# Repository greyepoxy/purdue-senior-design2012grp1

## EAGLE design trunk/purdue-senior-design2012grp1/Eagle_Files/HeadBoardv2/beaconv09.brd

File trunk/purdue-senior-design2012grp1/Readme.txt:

Please place code for the different chips in different folders with the chip name or an alias as the name of the folder. 
Also please place schematic drawings and PCB files in these folders as well.

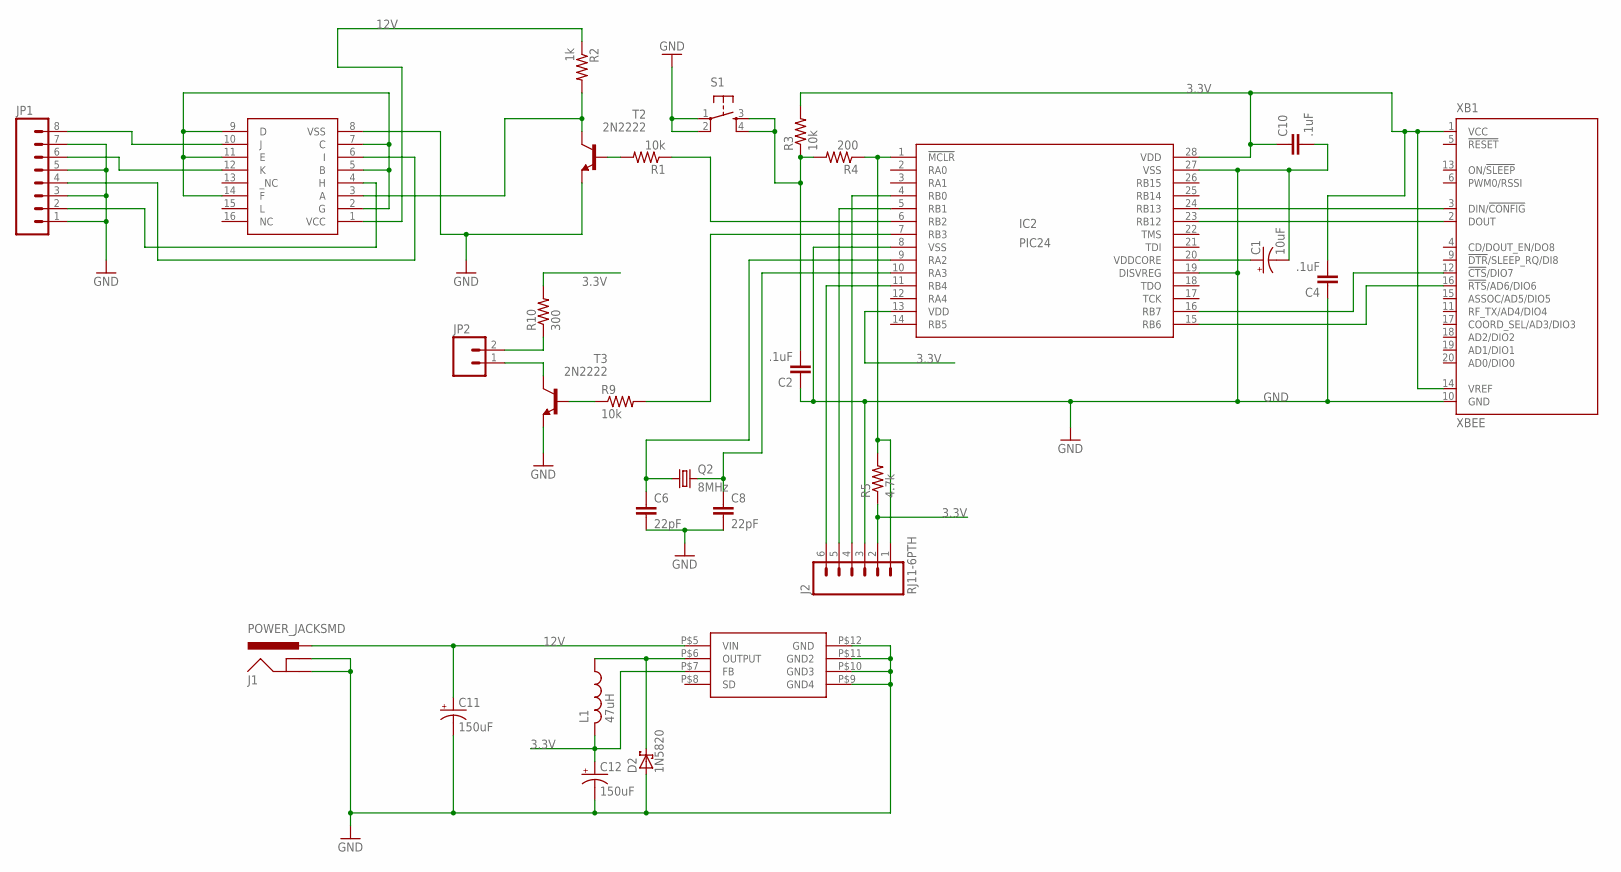
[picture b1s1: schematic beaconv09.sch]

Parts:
AP1509: BUCK1; BUCK
C1: 10uF; EIA3216
C2, C4, C10: .1uF; C1206
C6, C8: 22pF; C1206
C11, C12: 150uF; ECAPSMPS
D2: 1N5820; DO201T15
IC2: PIC24; SO28W
J1: POWER_JACKSMD; POWER_JACK_SMD
J2: RJ11-6PTH; RJ11-6
JP1: M08LOCK; 1X08_LOCK
JP2: M02LOCK; 1X02_LOCK
L1: 47uH; BUCKINDUCTOR2
Q2: 8MHz; HC49UP
R1, R3: 10k; 1206
R2: 1k; 1206
R4: 200; 1206
R5: 4.7k; R1206
R9: 10k; R1206
R10: 300; R1206
S1: TAC_SWITCHSMD; TACTILE_SWITCH_SMD
T2, T3: 2N2222; TO92-CBE
U$2: CD4049; DIL16
XB1: XBEE

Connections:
3.3V: AP1509.P$7 (FB), C4.2, C10.1, C12.P$1 (+), IC2.13 (VDD), IC2.28 (VDD), J2.2, L1.P$2 (2), R3.2, R5.1, R10.2, XB1.1 (VCC), XB1.14 (VREF)
12V: AP1509.P$5 (VIN), C11.P$1 (+), J1.VIN0 (PWR), R2.1, U$2.1 (VCC)
GND: AP1509.P$9 (GND4), AP1509.P$10 (GND3), AP1509.P$11 (GND2), AP1509.P$12 (GND), C1.C (-), C2.1, C4.1, C6.2, C8.2, C10.2, C11.P$2 (-), C12.P$2 (-), D2.A, IC2.8 (VSS), IC2.19 (DISVREG), IC2.27 (VSS), J1.GND (GNDBREAK), J1.P$4 (GND), J2.3, JP1.1, JP1.3, JP1.5, JP1.7, S1.1, S1.2, T2.E, T3.E, U$2.8 (VSS), XB1.10 (GND)
unnamed: IC2.6 (RB2), R1.1
unnamed: R1.2, T2.B
unnamed: JP1.2, U$2.4 (H)
unnamed: JP2.2, R10.1
unnamed: JP1.4, U$2.6 (I)
unnamed: IC2.23 (RB12), XB1.2 (DOUT)
unnamed: JP1.8, U$2.10 (J)
unnamed: IC2.24 (RB13), XB1.3 (DIN/!CONFIG)
unnamed: IC2.4 (RB0), J2.4
unnamed: C1.A (+), IC2.20 (VDDCORE)
unnamed: C2.2, R3.1, R4.2, S1.3, S1.4
unnamed: IC2.1 (!MCLR), J2.1, R4.1, R5.2
unnamed: IC2.16 (RB7), XB1.12 (!CTS!/DIO7)
unnamed: AP1509.P$6 (OUTPUT), D2.C, L1.P$1 (1)
unnamed: R2.2, T2.C, U$2.3 (A)
unnamed: IC2.7 (RB3), R9.2
unnamed: JP1.6, U$2.12 (K)
unnamed: JP2.1, T3.C
unnamed: IC2.5 (RB1), J2.5
unnamed: IC2.11 (RB4), J2.6
unnamed: U$2.2 (G), U$2.5 (B), U$2.7 (C), U$2.9 (D), U$2.11 (E), U$2.14 (F)
unnamed: C6.1, IC2.9 (RA2), Q2.1
unnamed: IC2.15 (RB6), XB1.16 (!RTS!/AD6/DIO6)
unnamed: C8.1, IC2.10 (RA3), Q2.2
unnamed: R9.1, T3.B

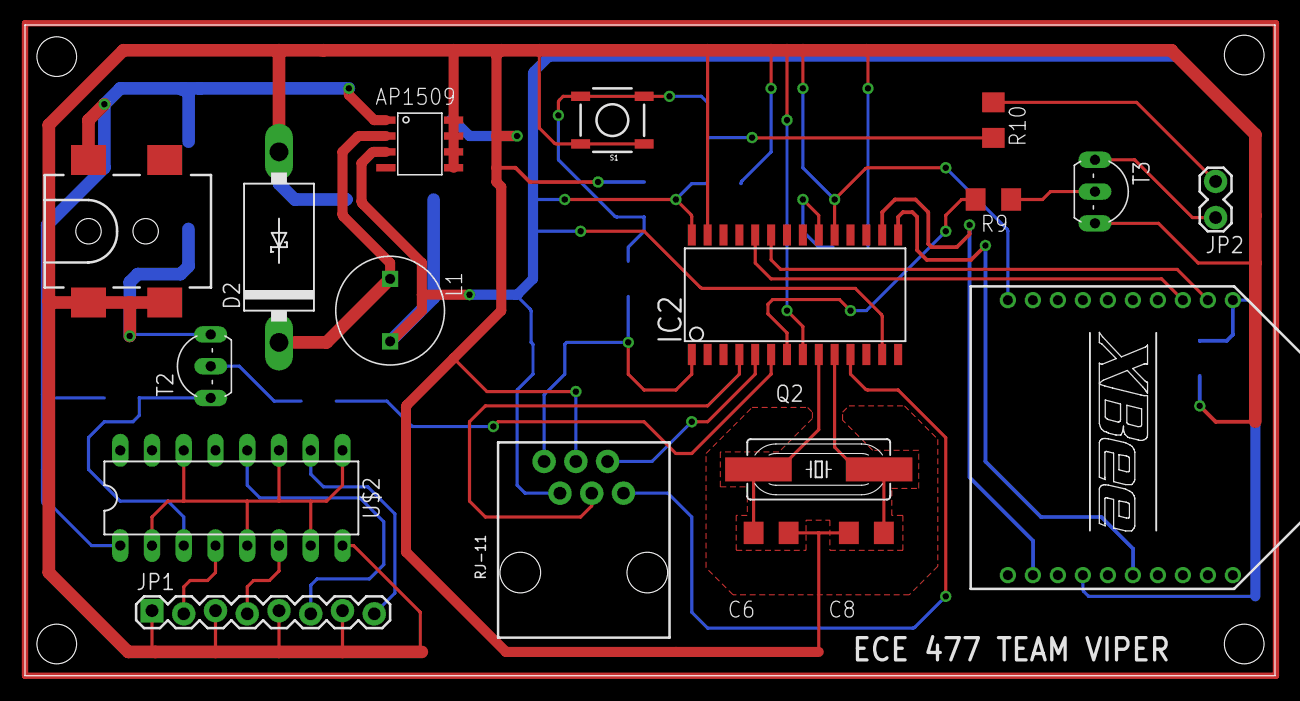
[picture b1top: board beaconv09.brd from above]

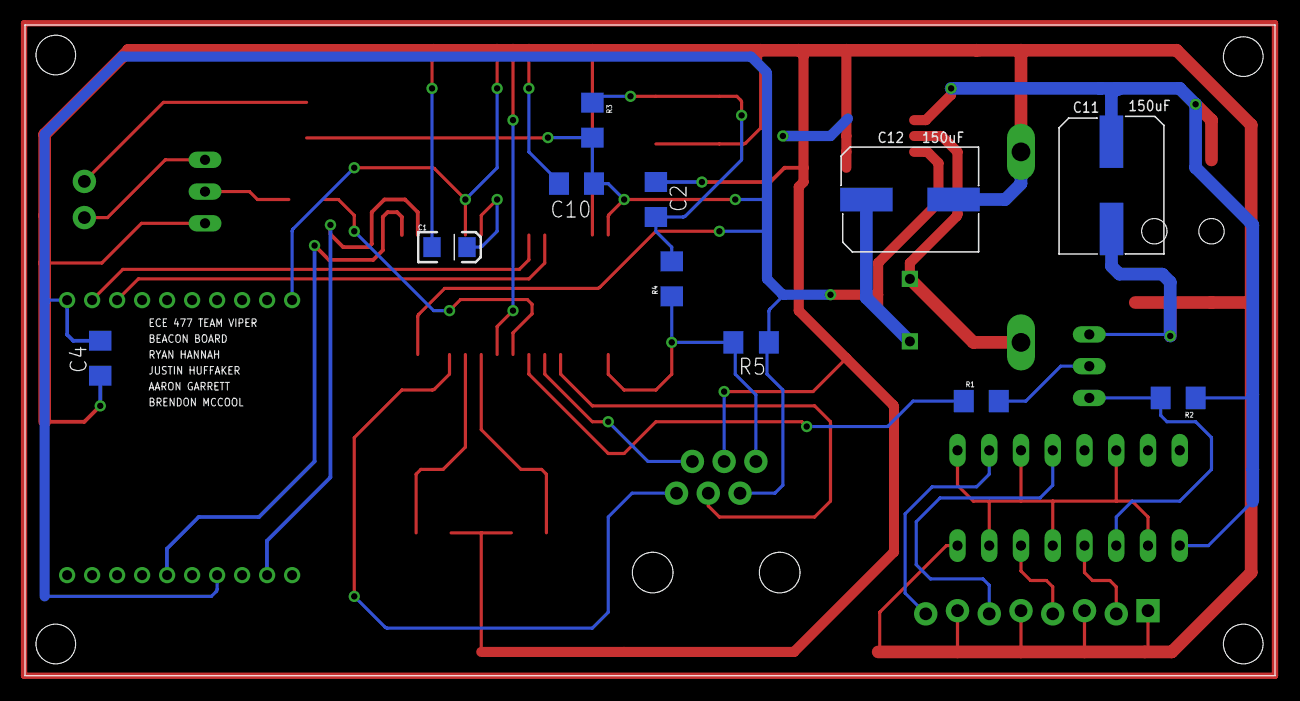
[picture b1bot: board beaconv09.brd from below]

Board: 2 copper layers, 100.0 x 52.1 mm, 29 parts (11 on the bottom side), 28 nets.

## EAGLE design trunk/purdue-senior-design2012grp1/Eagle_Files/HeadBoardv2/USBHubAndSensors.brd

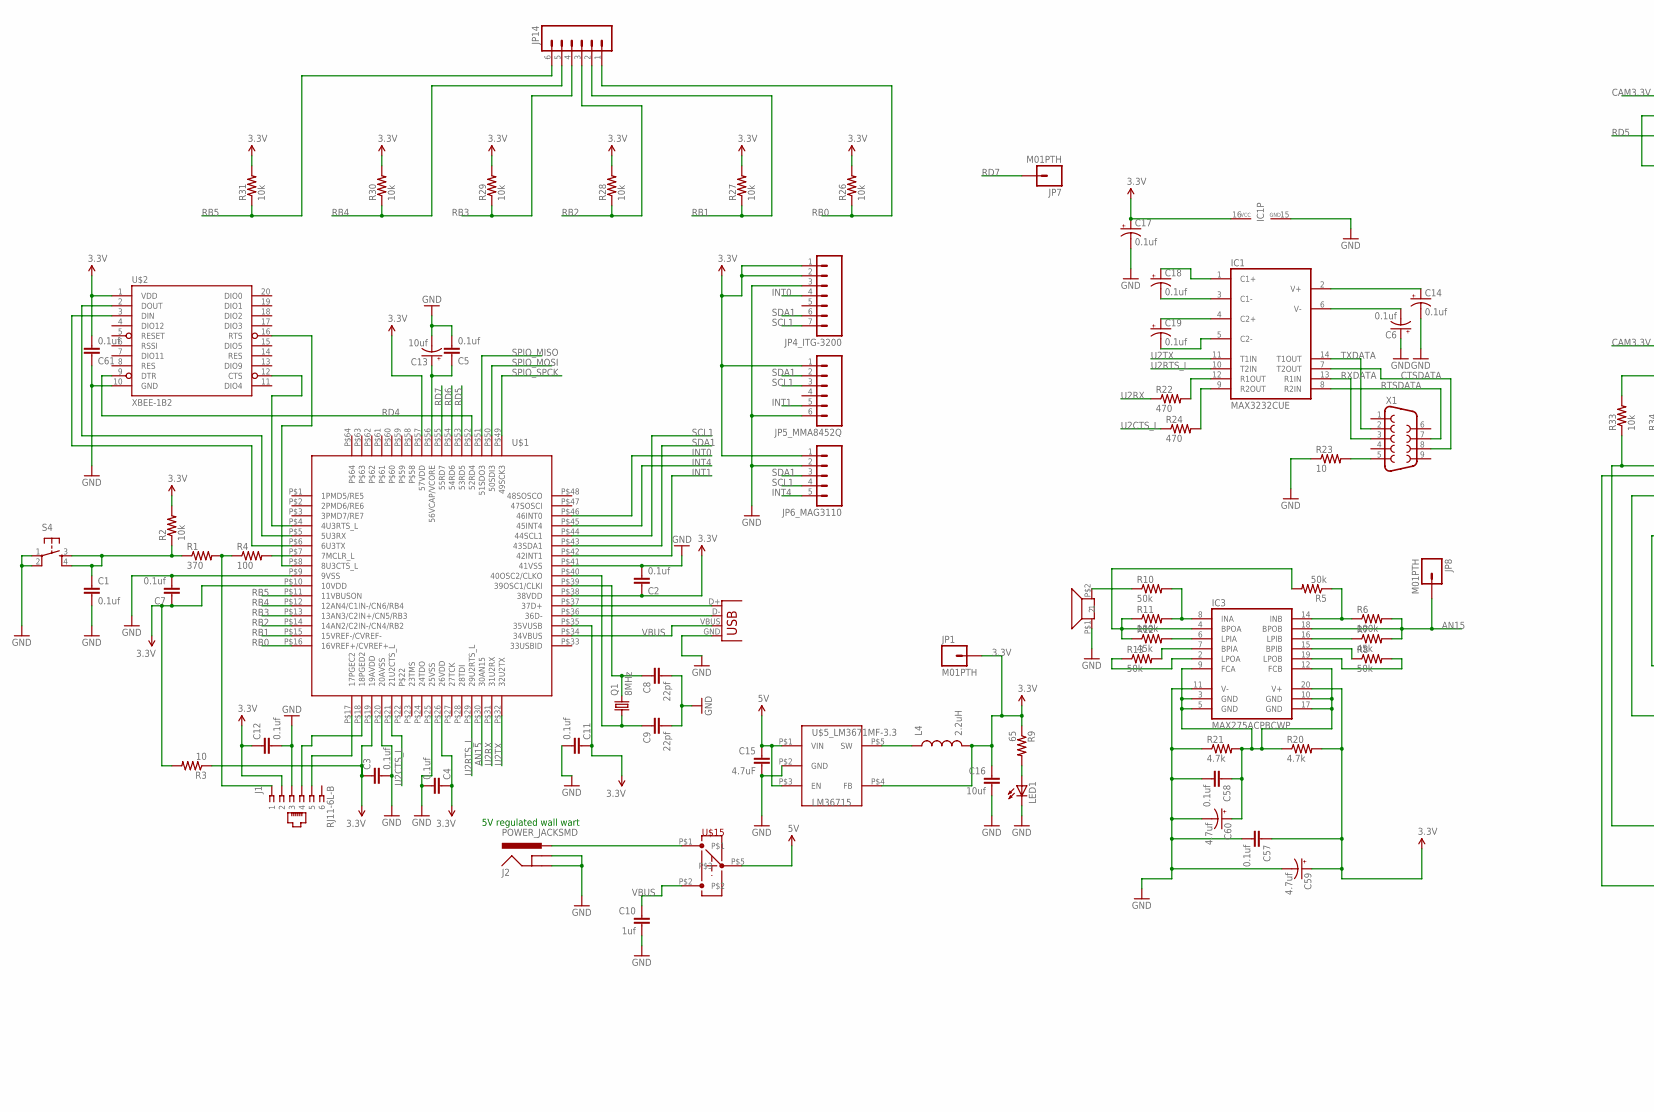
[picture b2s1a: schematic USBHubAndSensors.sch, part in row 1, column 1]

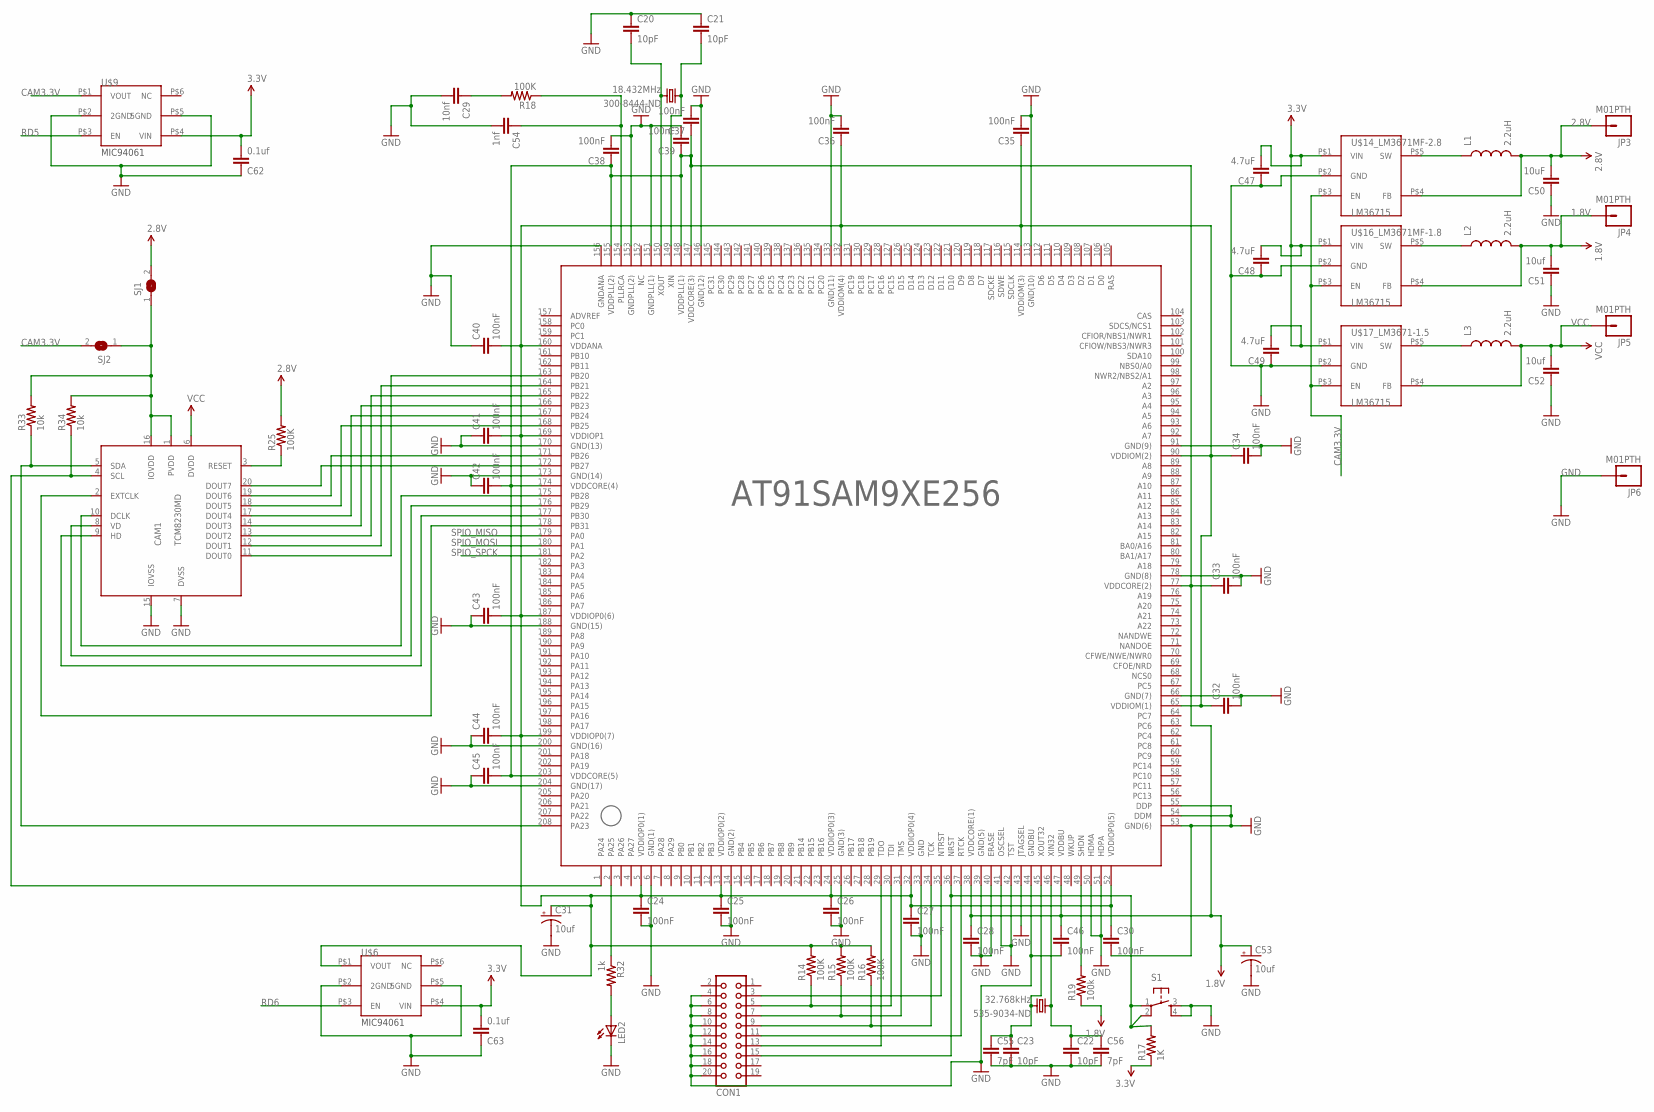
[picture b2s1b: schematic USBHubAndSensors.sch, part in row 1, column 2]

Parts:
300-8444-ND: 18.432MHz; TC38H
535-9034-ND: 32.768kHz; TC38H
C1, C2, C3, C4, C5, C7, C11, C12, C57, C58, C61, C62, C63: 0.1uf; 1206
C6, C14, C17, C18, C19: 0.1uf; EIA3216
C8, C9: 22pf; 1206
C10: 1uf; 1206
C13, C31, C53: 10uf; EIA3216
C15, C47, C48, C49: 4.7uF; 1206
C16, C51, C52: 10uf; 1206
C20, C21, C22, C23: 10pF; 1206
C24, C25, C26, C27, C28, C30, C32, C33, C34, C35, C36, C37, C38, C39, C40, C41, C42, C43, C44, C45, C46: 100nF; 1206
C29: 10nf; 1206
C50: 10uF; 1206
C54: 1nf; 1206
C55, C56: 7pF; 1206
C59, C60: 4.7uf; EIA3216
CAM1: TCM8230MD
CON1: CON20
IC1: MAX3232CUE; TSSOP16
IC3: MAX275ACPBCWP; SO20L
J1: RJ11-6L-B; RJ11-NO_SHIELD
J2: POWER_JACKSMD; POWER_JACK_SMD
JP1, JP3, JP4, JP5, JP6, JP7, JP8: M01PTH; 1X01
JP4_ITG-3200: M07; 1X07
JP5_MMA8452Q, JP14: M06SIP; 1X06
JP6_MAG3110: M05PTH; 1X05
L1, L2, L3, L4: 2.2uH; 1210
LED1, LED2: LED-FKIT-1206; FKIT-LED-1206
Q1: 8MHz; HC49UP
R1: 370; 1206
R2, R26, R27, R28, R29, R30, R31, R33, R34: 10k; 1206
R3, R23: 10; 1206
R4: 100; 1206
R5, R8, R10, R13: 50k; 1206
R6, R11, R19: 100k; 1206
R7, R12: 45k; 1206
R9: 65; 1206
R14, R15, R16, R18, R25: 100K; 1206
R17: 1K; 1206
R20, R21: 4.7k; 1206
R22, R24: 470; 1206
R32: 1k; 1206
S1, S4: TAC_SWITCHPTH; TACTILE-PTH
SJ1, SJ2: SJ
U$1: PIC32MX534F06HTQFP; 64-TQFP
U$2: XBEE-1B2; XBEE-SILK
U$5: 40TR-12B; 40TR
U$5_LM3671MF-3.3, U$14_LM3671MF-2.8, U$16_LM3671MF-1.8, U$17_LM3671-1.5: LM36715; SOT23-5
U$6, U$9: MIC94061YC6; SC-70-6
U$7: AT91SAM9XE256; PQFP208
U$15: G-107PLUG-IN; G-197
X1: DB9FEMALE; DB9
X2: USB-MICROB

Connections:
1.8V: C28.1, C33.1, C37.1, C38.1, C39.1, C42.2, C45.2, C46.1, C51.2, C53.A (+), JP4.1, L2.2, R19.1, U$7.38 (VDDCORE(1)), U$7.47 (VDDBU), U$7.77 (VDDCORE(2)), U$7.147 (VDDCORE(3)), U$7.148 (VDDPLL(1)), U$7.155 (VDDPLL(2)), U$7.174 (VDDCORE(4)), U$7.203 (VDDCORE(5)), U$16_LM3671MF-1.8.P$4 (FB)
2.8V: C50.2, JP3.1, L1.2, R25.2, SJ1.2, U$14_LM3671MF-2.8.P$4 (FB)
3.3V: C2.1, C3.1, C4.1, C7.1, C11.1, C12.1, C16.1, C17.A (+), C47.2, C48.2, C49.2, C57.1, C59.A (+), C61.2, C62.2, C63.2, IC1.16 (VCC), IC3.20 (V+), J1.2, JP1.1, JP4_ITG-3200.1, JP4_ITG-3200.2, JP5_MMA8452Q.1, JP6_MAG3110.1, L4.2, R2.2, R3.1, R3.2, R9.1, R17.1, R20.2, R26.2, R27.2, R28.2, R29.2, R30.2, R31.2, U$1.P$10 (10VDD), U$1.P$19 (19AVDD), U$1.P$26 (26VDD), U$1.P$35 (35VUSB), U$1.P$38 (38VDD), U$1.P$57 (57VDD), U$2.1 (VDD), U$5_LM3671MF-3.3.P$4 (FB), U$6.P$4 (VIN), U$9.P$4 (VIN), U$14_LM3671MF-2.8.P$1 (VIN), U$16_LM3671MF-1.8.P$1 (VIN), U$17_LM3671-1.5.P$1 (VIN)
5V: C15.1, U$5_LM3671MF-3.3.P$1 (VIN), U$5_LM3671MF-3.3.P$3 (EN), U$15.P$5
AN15: IC3.18 (BPOB), JP8.1, R6.2, R7.2, U$1.P$30 (30AN15)
CAM3.3V: SJ2.2, U$9.P$1 (VOUT), U$14_LM3671MF-2.8.P$3 (EN), U$16_LM3671MF-1.8.P$3 (EN), U$17_LM3671-1.5.P$3 (EN)
CTSDATA: IC1.7 (T2OUT), X1.8
GND: C1.2, C2.2, C3.2, C4.2, C5.2, C6.A (+), C7.2, C8.2, C9.2, C10.2, C11.2, C12.2, C13.C (-), C14.C (-), C15.2, C16.2, C17.C (-), C20.1, C21.1, C22.2, C23.2, C24.2, C25.2, C26.2, C27.2, C28.2, C29.2, C30.2, C31.C (-), C32.2, C33.2, C34.2, C35.2, C36.2, C37.2, C38.2, C39.2, C40.1, C41.1, C42.1, C43.1, C44.1, C45.1, C46.2, C47.1, C48.1, C49.1, C50.1, C51.1, C52.1, C53.C (-), C54.2, C55.2, C56.2, C57.2, C58.2, C59.C (-), C60.C (-), C61.1, C62.1, C63.1, CAM1.7 (DVSS), CAM1.15 (IOVSS), CON1.4, CON1.6, CON1.8, CON1.10, CON1.12, CON1.14, CON1.16, CON1.18, CON1.20, IC1.15 (GND), IC3.11 (V-), J1.3, J2.GND (GNDBREAK), J2.P$4 (GND), JP4_ITG-3200.3, JP5_MMA8452Q.6, JP6.1, JP6_MAG3110.2, LED1.C, LED2.C, R21.1, R23.1, S1.3, S1.4, S4.1, S4.2, U$1.P$9 (9VSS), U$1.P$20 (20AVSS), U$1.P$25 (25VSS), U$1.P$41 (41VSS), U$2.10 (GND), U$5.P$1 (1), U$5_LM3671MF-3.3.P$2 (GND), U$6.P$2 (2GND), U$6.P$5 (5GND), U$7.6 (GND(1)), U$7.14 (GND(2)), U$7.25 (GND(3)), U$7.33 (GND), U$7.39 (GND(5)), U$7.40 (ERASE), U$7.41 (OSCSEL), U$7.42 (TST), U$7.43 (JTAGSEL), U$7.44 (GNDBU), U$7.50 (HDMA), U$7.51 (HDPA), U$7.53 (GND(6)), U$7.54 (DDM), U$7.55 (DDP), U$7.66 (GND(7)), U$7.78 (GND(8)), U$7.91 (GND(9)), U$7.113 (GND(10)), U$7.133 (GND(11)), U$7.146 (GND(12)), U$7.151 (GNDPLL(1)), U$7.153 (GNDPLL(2)), U$7.156 (GNDANA), U$7.170 (GND(13)), U$7.173 (GND(14)), U$7.188 (GND(15)), U$7.200 (GND(16)), U$7.204 (GND(17)), U$9.P$2 (2GND), U$9.P$5 (5GND), U$14_LM3671MF-2.8.P$2 (GND), U$16_LM3671MF-1.8.P$2 (GND), U$17_LM3671-1.5.P$2 (GND), X2.GND
INT0: JP4_ITG-3200.4, U$1.P$46 (46INT0)
INT1: JP5_MMA8452Q.5, U$1.P$42 (42INT1)
INT4: JP6_MAG3110.5, U$1.P$45 (45INT4)
unnamed: C1.1, R1.1, R2.1, S4.3, S4.4
unnamed: C24.1, C25.1, C26.1, C27.1, C30.1, C31.A (+), C32.1, C34.1, C35.1, C36.1, C40.2, C41.2, C43.2, C44.2, R14.2, R15.2, R16.2, U$6.P$1 (VOUT), U$7.5 (VDDIOP0(1)), U$7.13 (VDDIOP0(2)), U$7.24 (VDDIOP0(3)), U$7.32 (VDDIOP0(4)), U$7.52 (VDDIOP0(5)), U$7.65 (VDDIOM(1)), U$7.90 (VDDIOM(2)), U$7.114 (VDDIOM(3)), U$7.132 (VDDIOM(4)), U$7.160 (VDDANA), U$7.169 (VDDIOP1), U$7.187 (VDDIOP0(6)), U$7.199 (VDDIOP0(7))
unnamed: J1.4, U$1.P$18 (18PGED2)
unnamed: C9.1, Q1.1, U$1.P$40 (40OSC2/CLKO)
unnamed: C8.1, Q1.2, U$1.P$39 (39OSC1/CLKI)
unnamed: R4.2, U$1.P$7 (7MCLR_L)
unnamed: J1.5, U$1.P$17 (17PGEC2)
unnamed: L4.1, U$5_LM3671MF-3.3.P$5 (SW)
unnamed: U$1.P$6 (6U3TX), U$2.3 (DIN)
unnamed: C18.A (+), IC1.1 (C1+)
unnamed: C18.C (-), IC1.3 (C1-)
unnamed: C19.A (+), IC1.4 (C2+)
unnamed: C5.1, C13.A (+), U$1.P$56 (56VCAP/VCORE)
unnamed: U$1.P$36 (36D-), X2.D-
unnamed: U$1.P$37 (37D+), X2.D+
unnamed: C19.C (-), IC1.5 (C2-)
unnamed: U$1.P$5 (5U3RX), U$2.2 (DOUT)
unnamed: U$1.P$8 (8U3CTS_L), U$2.16 (RTS)
unnamed: U$1.P$4 (4U3RTS_L), U$2.12 (CTS)
unnamed: CON1.11, U$7.37 (RTCK)
unnamed: J1.1, R1.2, R4.1
unnamed: CAM1.3 (RESET), R25.1
unnamed: C14.A (+), IC1.2 (V+)
unnamed: C6.C (-), IC1.6 (V-)
unnamed: IC3.14 (INB), R5.1, R6.1
unnamed: R10.1, U$5.P$2 (2)
unnamed: IC3.16 (LPIB), R7.1
unnamed: LED1.A, R9.2
unnamed: IC3.15 (BPIB), R8.1
unnamed: IC3.19 (LPOB), R8.2
unnamed: IC3.2 (LPOA), R13.1
unnamed: IC3.7 (BPIA), R13.2
unnamed: IC3.6 (LPIA), R12.2
unnamed: IC3.8 (INA), R10.2, R11.2
unnamed: IC3.4 (BPOA), R5.2, R11.1, R12.1
unnamed: CAM1.11 (DOUT0), U$7.163 (PB20)
unnamed: CAM1.12 (DOUT1), U$7.164 (PB21)
unnamed: CAM1.13 (DOUT2), U$7.165 (PB22)
unnamed: CAM1.14 (DOUT3), U$7.166 (PB23)
unnamed: CAM1.17 (DOUT4), U$7.167 (PB24)
unnamed: CAM1.18 (DOUT5), U$7.168 (PB25)
unnamed: CAM1.19 (DOUT6), U$7.171 (PB26)
unnamed: CAM1.20 (DOUT7), U$7.172 (PB27)
unnamed: CAM1.10 (DCLK), U$7.175 (PB28)
unnamed: CAM1.8 (VD), U$7.176 (PB29)
unnamed: CAM1.9 (HD), U$7.177 (PB30)
unnamed: CAM1.2 (EXTCLK), U$7.178 (PB31)
unnamed: CAM1.4 (SCL), R34.1, U$7.1 (PA24)
unnamed: CAM1.5 (SDA), R33.1, U$7.208 (PA23)
unnamed: 300-8444-ND.1, C21.2, U$7.149 (XIN)
unnamed: 300-8444-ND.2, C20.2, U$7.150 (XOUT)
unnamed: 535-9034-ND.1, C22.1, C56.1, U$7.46 (XIN32)
unnamed: 535-9034-ND.2, C23.1, C55.1, U$7.45 (XOUT32)
unnamed: CON1.5, R14.1, U$7.30 (TDI)
unnamed: CON1.7, R15.1, U$7.31 (TMS)
unnamed: CON1.9, R16.1, U$7.34 (TCK)
unnamed: CON1.13, U$7.29 (TDO)
unnamed: CON1.3, U$7.35 (NTRST)
unnamed: CAM1.1 (PVDD), CAM1.16 (IOVDD), R33.2, R34.2, SJ1.1, SJ2.1
unnamed: L1.1, U$14_LM3671MF-2.8.P$5 (SW)
unnamed: L2.1, U$16_LM3671MF-1.8.P$5 (SW)
unnamed: L3.1, U$17_LM3671-1.5.P$5 (SW)
unnamed: C54.1, R18.1, U$7.154 (PLLRCA)
unnamed: C29.1, R18.2
unnamed: R19.2, U$7.49 (SHDN)
unnamed: J2.VIN0 (PWR), U$15.P$1
unnamed: IC1.12 (R1OUT), R22.2
unnamed: C58.1, C60.A (+), IC3.3 (GND), IC3.5 (GND), IC3.9 (FCA), IC3.10 (GND), IC3.12 (FCB), IC3.17 (GND), R20.1, R21.2
unnamed: R23.2, X1.5
unnamed: R32.1, U$7.2 (PA25)
unnamed: IC1.9 (R2OUT), R24.2
unnamed: LED2.A, R32.2
unnamed: CON1.15, R17.2, S1.1, S1.2, U$7.36 (NRST)
RB0: JP14.1, R26.1, U$1.P$16 (16VREF+/CVREF+)
RB1: JP14.2, R27.1, U$1.P$15 (15VREF-/CVREF-)
RB2: JP14.3, R28.1, U$1.P$14 (14AN2/C2IN-/CN4/RB2)
RB3: JP14.4, R29.1, U$1.P$13 (13AN3/C2IN+/CN5/RB3)
RB4: JP14.5, R30.1, U$1.P$12 (12AN4/C1IN-/CN6/RB4)
RB5: JP14.6, R31.1, U$1.P$11 (11VBUSON)
RD4: U$1.P$52 (52RD4), U$2.9 (DTR)
RD5: U$1.P$53 (53RD5), U$9.P$3 (EN)
RD6: U$1.P$54 (54RD6), U$6.P$3 (EN)
RD7: JP7.1, U$1.P$55 (55RD7)
RTSDATA: IC1.8 (R2IN), X1.7
RXDATA: IC1.13 (R1IN), X1.3
SCL1: JP4_ITG-3200.7, JP5_MMA8452Q.3, JP6_MAG3110.4, U$1.P$44 (44SCL1)
SDA1: JP4_ITG-3200.6, JP5_MMA8452Q.2, JP6_MAG3110.3, U$1.P$43 (43SDA1)
SPIO_MISO: U$1.P$51 (51SDO3), U$7.179 (PA0)
SPIO_MOSI: U$1.P$50 (50SDI3), U$7.180 (PA1)
SPIO_SPCK: U$1.P$49 (49SCK3), U$7.181 (PA2)
TXDATA: IC1.14 (T1OUT), X1.2
U2CTS_L: R24.1, U$1.P$21 (21U2CTS_L)
U2RTS_L: IC1.10 (T2IN), U$1.P$29 (29U2RTS_L)
U2RX: R22.1, U$1.P$31 (31U2RX)
U2TX: IC1.11 (T1IN), U$1.P$32 (32U2TX)
VBUS: C10.1, U$1.P$34 (34VBUS), U$15.P$2, X2.VBUS
VCC: C52.2, CAM1.6 (DVDD), JP5.1, L3.2, U$17_LM3671-1.5.P$4 (FB)

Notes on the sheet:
5V regulated wall wart

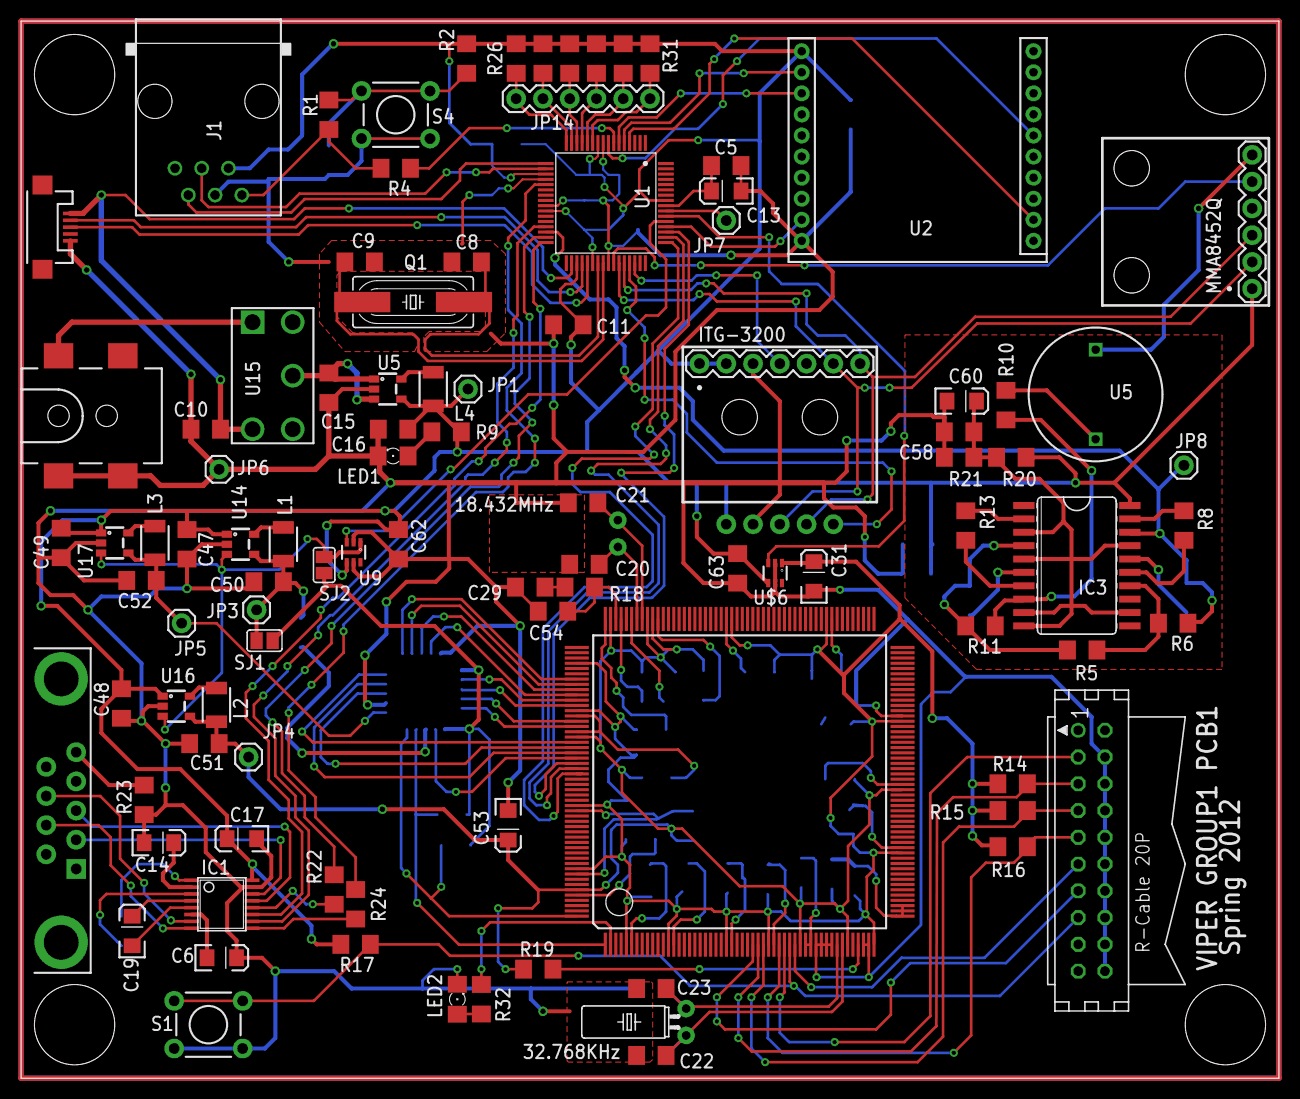
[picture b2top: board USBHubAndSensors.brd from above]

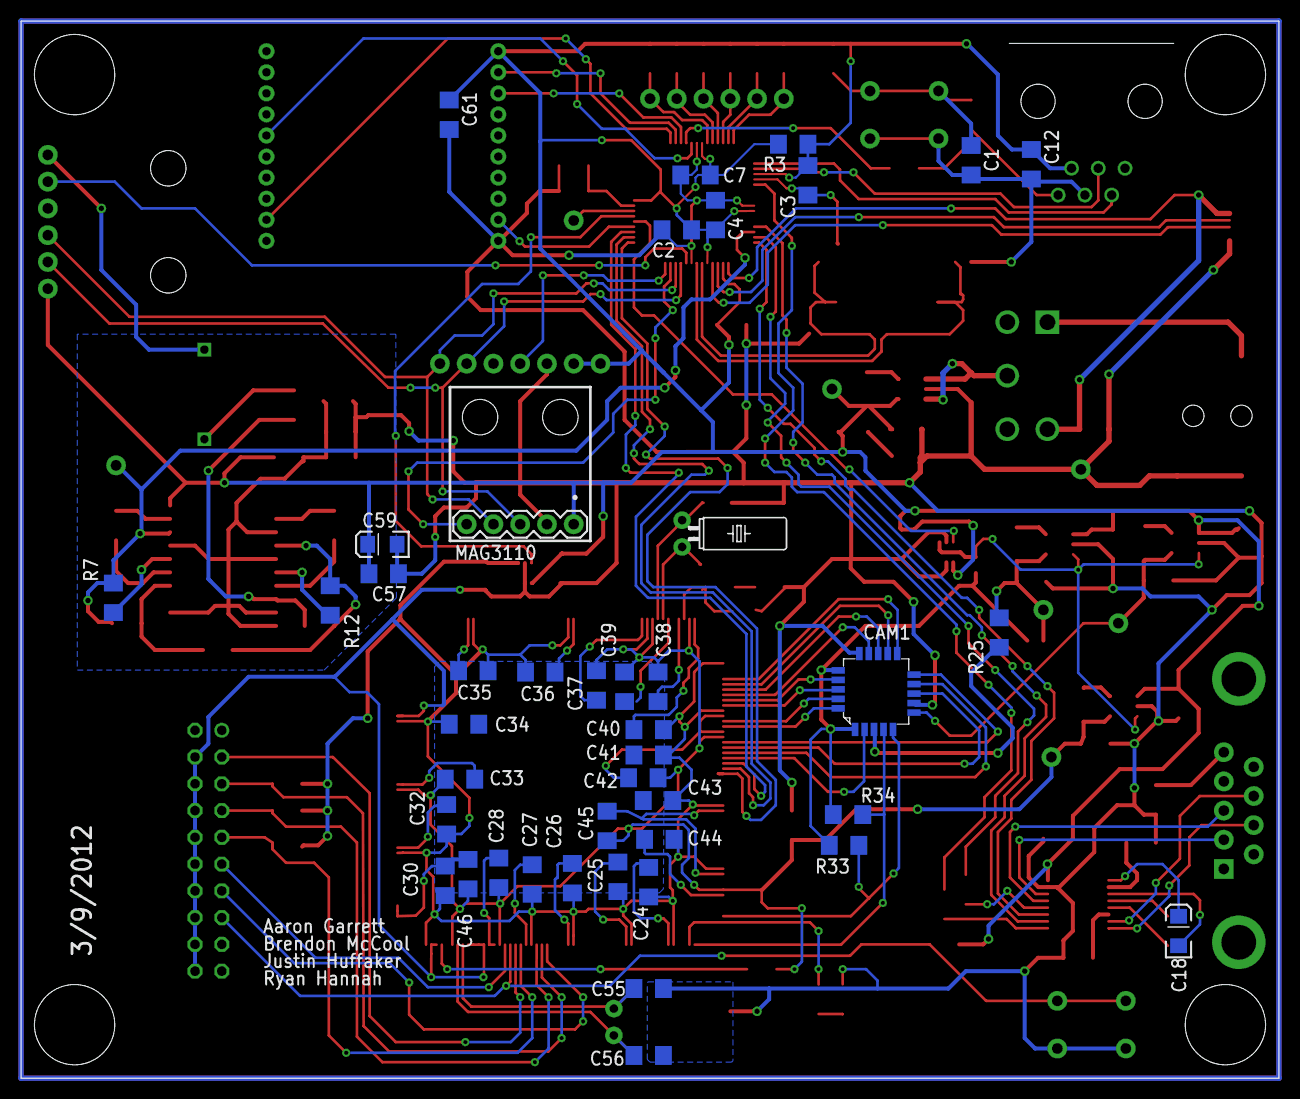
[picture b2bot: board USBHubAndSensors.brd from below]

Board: 2 copper layers, 119.4 x 100.3 mm, 140 parts (42 on the bottom side), 108 nets.

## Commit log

2012-02-04 Initial directory structure.
2012-02-04 Check to make sure everything is working, added simple rules to follow when committing in Readme.txt.
2012-02-22 default files to commit
2012-03-07 Added a bunch of code that performs I2C communication as well as PWM output, uart output, and has timer interrupt example
2012-03-20 renaming
2012-03-20 moving
2012-03-24 Able to take a picture.... Maybe?
2012-03-24 Backup of the Eagle schematics
2012-03-24 Eagles files a week after spring break
2012-04-09 Tested components with updated code, also implemented ADC10
2012-04-09 added interrupts.h
2012-04-10 Working on the PCB. Able to read data after the camera DMA.
2012-04-11 usb test program
2012-04-11 updated usb descriptor to reflect that device is not self powered
2012-04-13 Beagleboard qt code
2012-04-17 PIC24 Code
2012-04-17 New Code Pic24
2012-04-17 WORKING WITH WARHAL MODE
2012-04-17 Working with 4 sensors
2012-04-20 updated code to get usb connection working
2012-04-20 Queue Fixed?
2012-04-23 fixed sensor data and other stuff that I do not remember
2012-04-23 Final Working
2012-04-24 code with all PSSCs working, used complimentary filter
2015-03-14 Migrating wiki contents from Google Code

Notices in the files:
parts and their libraries:
SparkFun-Passives: Licensing: CC v3.0 Share-Alike You are welcome to use this library for commercial purposes.
